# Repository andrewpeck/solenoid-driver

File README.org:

** Single Channel Solenoid Driver

#+attr_org: :width 500px
[[file:./images/driver-v0.png]]

A prototype single channel solenoid driver was developed for testing.

It is contained in the ~driver-v0~ folder.

We will have 3 manifolds with 8 of these in a row that need to be driven with 12V and signalled with a TTL line. All the manifolds will act in unison.

 - https://www.theleeco.com/product/lhd-series-2-way-control-solenoid-valve/
 - 3 boards, 8 channels each
 - 8 TTL inputs + GND
 - 8 12V outputs
 - 12V input on barrel jack
   - Plug:
     - https://www.digikey.com/en/products/detail/globtek-inc/CRP11856F00/16515770
     - Cable Assembly 2.1mm ID, 5.5mm OD Jack, Right Angle to Wire Leads Round 6.0' (1.83m)
   - Jack:
     - https://www.digikey.com/en/products/detail/cui-devices/PJ-063AH/2161208
     - PJ-063AH Power Barrel Connector Jack 2.10mm ID (0.083"), 5.50mm OD (0.217") Through Hole, Right Angle
 - LHDB1242115H
 - Spike+hold voltage: 12, 7.2
 - LOHM RATE** (Cv): 1500 Lohms (0.013)
 - Power Consumption At Hold Voltage (mW): 310
 - Response time: 10 ms Max

|----+-----------+-----+----------------------+--------------------+---------------------------|
|  # | Reference | Qty | Value                | PartNum            | Mfg                       |
|----+-----------+-----+----------------------+--------------------+---------------------------|
|  1 | C1        |   1 | 47uF                 | T491X476K035AT     | Kemet                     |
|  2 | C3        |   1 | 10uF                 | CL32A106KLULNNE    | Samsung Electro-Mechanics |
|  3 | C4        |   1 | 0.18 uF              | 08053C184KAT2A     | KYOCERA AVX               |
|  4 | C5        |   1 | 470pF                | C0805C471K5RAC7800 | Kemet                     |
|  5 | D1        |   1 | LED                  | 150080RS75000      | Wurth                     |
|  6 | D2        |   1 | PMEG10010ELRX        | PMEG10010ELRX      | Nexperia                  |
|  7 | F1        |   1 | 0ZCF0125FF2C         | 0ZCF0125FF2C       | Bel Fuse                  |
|  8 | J1, J2    |   2 | Screw_Terminal_01x02 | 282837-2           | TE                        |
|  9 | J3        |   1 | Barrel_Jack          | PJ-063AH           | CUI                       |
| 10 | R1        |   1 | 49R9                 | RC0805FR-0749R9L   | Yageo                     |
| 11 | R2        |   1 | 191k                 | RC0805FR-07191KL   | Yageo                     |
| 12 | R3        |   1 | 162k                 | RC0805FR-07162KL   | Yageo                     |
| 13 | R4, R5    |   2 | 4k7                  | RC0805JR-074K7L    | Yageo                     |
| 14 | U1        |   1 | DRV104PWP            | DRV104PWP          | TI                        |
|----+-----------+-----+----------------------+--------------------+---------------------------|

** Octal Channel Driver

** Dual Channel Complementary Driver

We will also have a pair of these valves that need to be driven by a single TTL
line in opposition (if one is in state A the other should be in state B).
 - LHDA1231415H
 - https://www.theleeco.com/product/lhd-series-3-way-control-solenoid-valve/
 - One TTL input  + GND
 - Two 12V complementary outputs

The solenoids should be driven with a high-side switch using a peak and hold circuit.

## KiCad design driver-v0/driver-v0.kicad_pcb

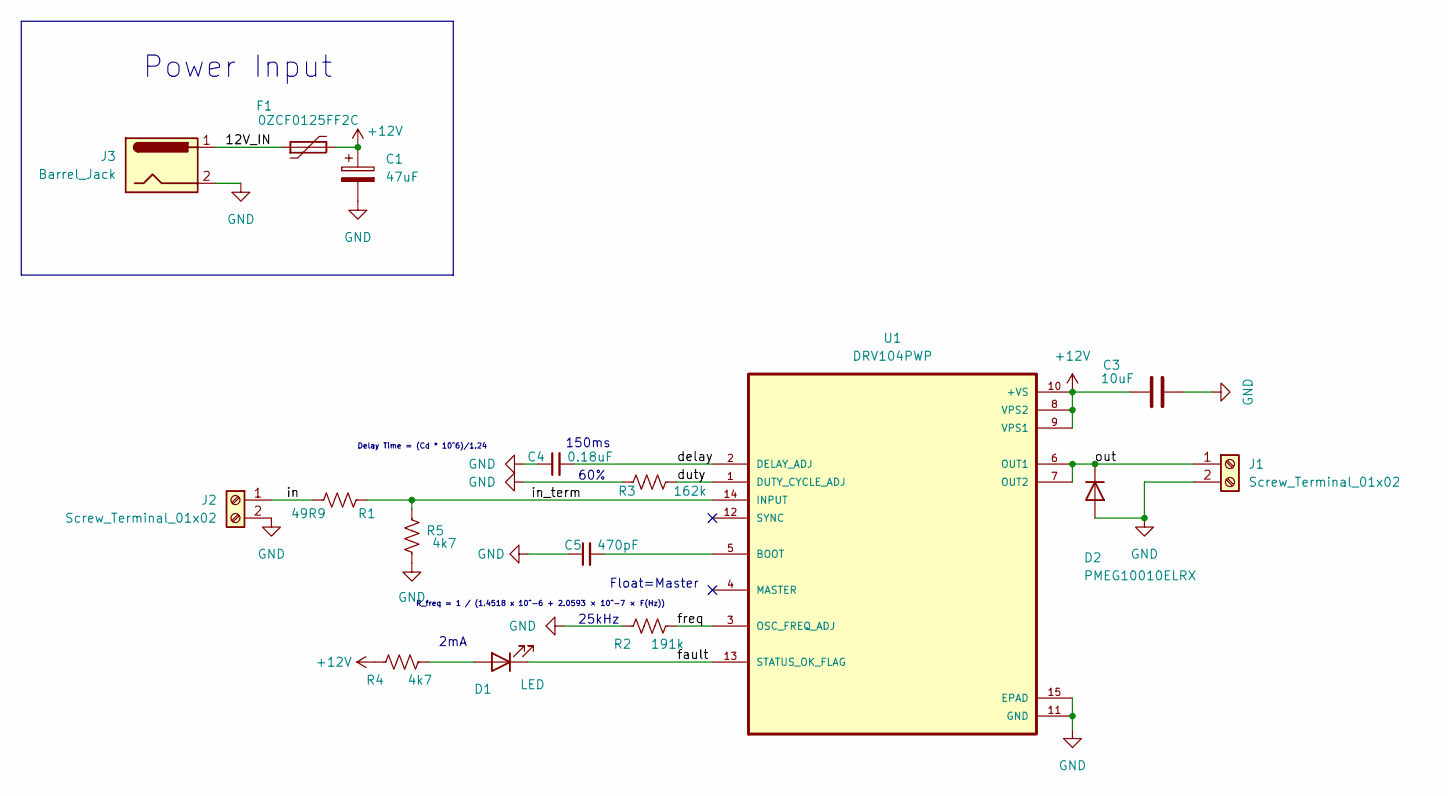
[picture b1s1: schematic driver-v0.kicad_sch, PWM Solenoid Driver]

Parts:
C1: 47uF; CP_EIA-7343-43_Kemet-X_Pad2.25x2.55mm_HandSolder; PartNum T491X476K035AT
C3: 10uF; C_1210_3225Metric; PartNum CL32A106KLULNNE
C4: 0.18uF; C_0805_2012Metric; PartNum 08053C184KAT2A
C5: 470pF; C_0805_2012Metric; PartNum C0805C471K5RAC7800
D1: LED; LED_0805_2012Metric; PartNum 150080RS75000
D2: PMEG10010ELRX; Nexperia_CFP3_SOD-123W; PartNum PMEG10010ELRX
F1: 0ZCF0125FF2C; Fuse_2920_7451Metric; PartNum 0ZCF0125FF2C
J1, J2: Screw_Terminal_01x02; TerminalBlock_bornier-2_P5.08mm; PartNum 282837-2
J3: Barrel_Jack; BarrelJack_CUI_PJ-063AH_Horizontal; PartNum PJ-063AH
R1: 49R9; R_0805_2012Metric; PartNum RC0805FR-0749R9L
R2: 191k; R_0805_2012Metric; PartNum RC0805FR-07191KL
R3: 162k; R_0805_2012Metric; PartNum RC0805FR-07162KL
R4, R5: 4k7; R_0805_2012Metric; PartNum RC0805JR-074K7L
U1: DRV104PWP; IC_TPS27S100BPWPR; PartNum DRV104PWP

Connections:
+12V: C1.1, C3.1, F1.2, R4.1, U1.8 (VPS2), U1.9 (VPS1), U1.10 (+VS)
/12V_IN: F1.1, J3.1
/delay: C4.2, U1.2 (DELAY_ADJ)
/duty: R3.2, U1.1 (DUTY_CYCLE_ADJ)
/fault: D1.1 (K), U1.13 (STATUS_OK_FLAG)
/freq: R2.2, U1.3 (OSC_FREQ_ADJ)
/in: J2.1, R1.1
/in_term: R1.2, R5.2, U1.14 (INPUT)
/out: D2.1 (K), J1.1, U1.6 (OUT1), U1.7 (OUT2)
GND: C1.2, C3.2, C4.1, C5.1, D2.2 (A), J1.2, J2.2, J3.2, R2.1, R3.1, R5.1, U1.11 (GND), U1.15 (EPAD)
unnamed: D1.2 (A), R4.2
unnamed: C5.2, U1.5 (BOOT)

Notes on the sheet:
25kHz
Power Input
Float=Master
60%
R_freq = 1 / (1.4518 x 10^−6 + 2.0593 × 10^−7 × F(Hz))
2mA
150ms
Delay Time = (Cd * 10^6)/1.24

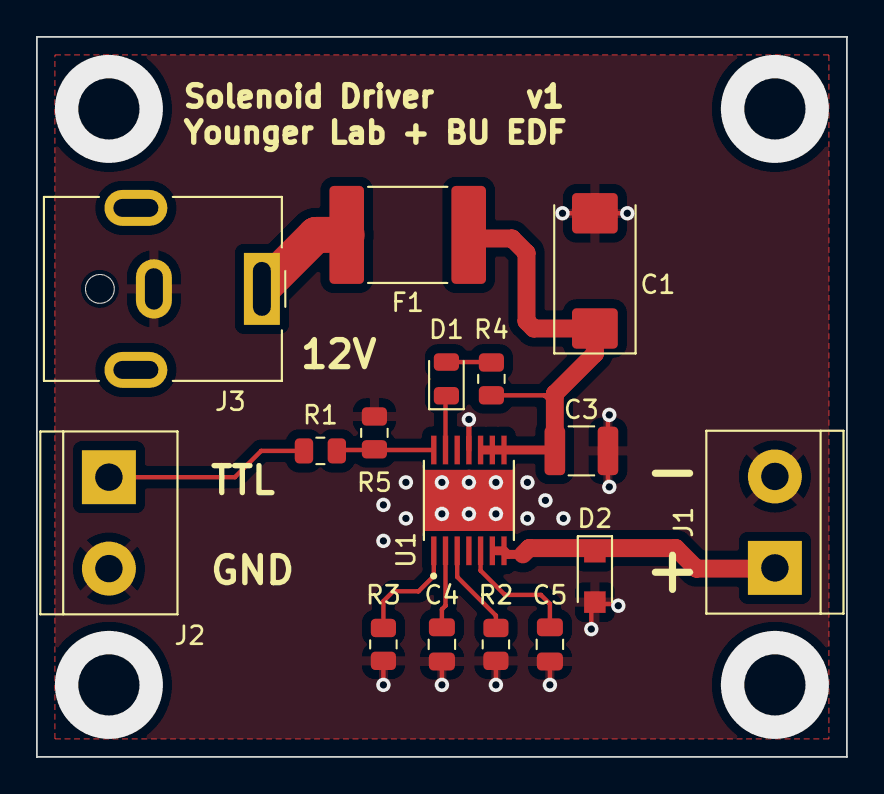
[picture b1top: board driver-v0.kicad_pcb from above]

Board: 2 copper layers, 45.0 x 40.0 mm, 16 parts (0 on the bottom side), 12 nets.

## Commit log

2023-07-21 init solenoid driver
2023-07-25 fix bom
2023-07-26 Add pdf schematic
2023-08-02 fix: change peak width from 150 us to 150 ms
    max switching time is 100 ms
